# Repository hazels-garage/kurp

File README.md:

# Kurp
## 36 Key unibody split ortholinear

## PCB Render

Kurp is a choc-spaced unibody split ortholinear keyboard.

## Materials

| Description | Part | Count | Notes |
| :---: | :---: | :---: | :---: |
| PCBs | [Main](pcbs/pcb/jlcpcb/production_files) | 1 | |
|| [Switchplate](pcbs/switchplate/jlcpcb/production_files) | 1 | Optional |
|| [Backplate](pcbs/backplate/jlcpcb/production_files) | 1 | Optional |
|| [Centerplate](pcbs/centerplate/jlcpcb/production_files) | 1 | Optional |
| Controller | ProMicro footprint | 1 |  | 
| Diodes | 1N4148 SOD-123  | 36 |  |
| Switches | Choc v1 | 36 |  | 
| Keycaps | 1u | 36 | |
| Reset | TL3342F260QG | 1 | |
| Display | SSD1306 | 1 | Optional |
| | nice!view |  | Wireless Only |
| Power Switch |  MSK-12C02 | 1 | Wireless Only | 
| Battery Connector | TBD | 1 | Optional, Wireless Only | 
| Battery | TBD | 1 | Wireless Only |
| 3mm M2 Standoff ||8||
| 9mm M2 Standoff ||4||
| 3mm M2 Screw ||24||

## Firmware
QMK : https://github.com/hazels-garage/qmk_firmware/tree/hazel/kurp

ZMK: https://github.com/hazels-garage/zmk-kurp

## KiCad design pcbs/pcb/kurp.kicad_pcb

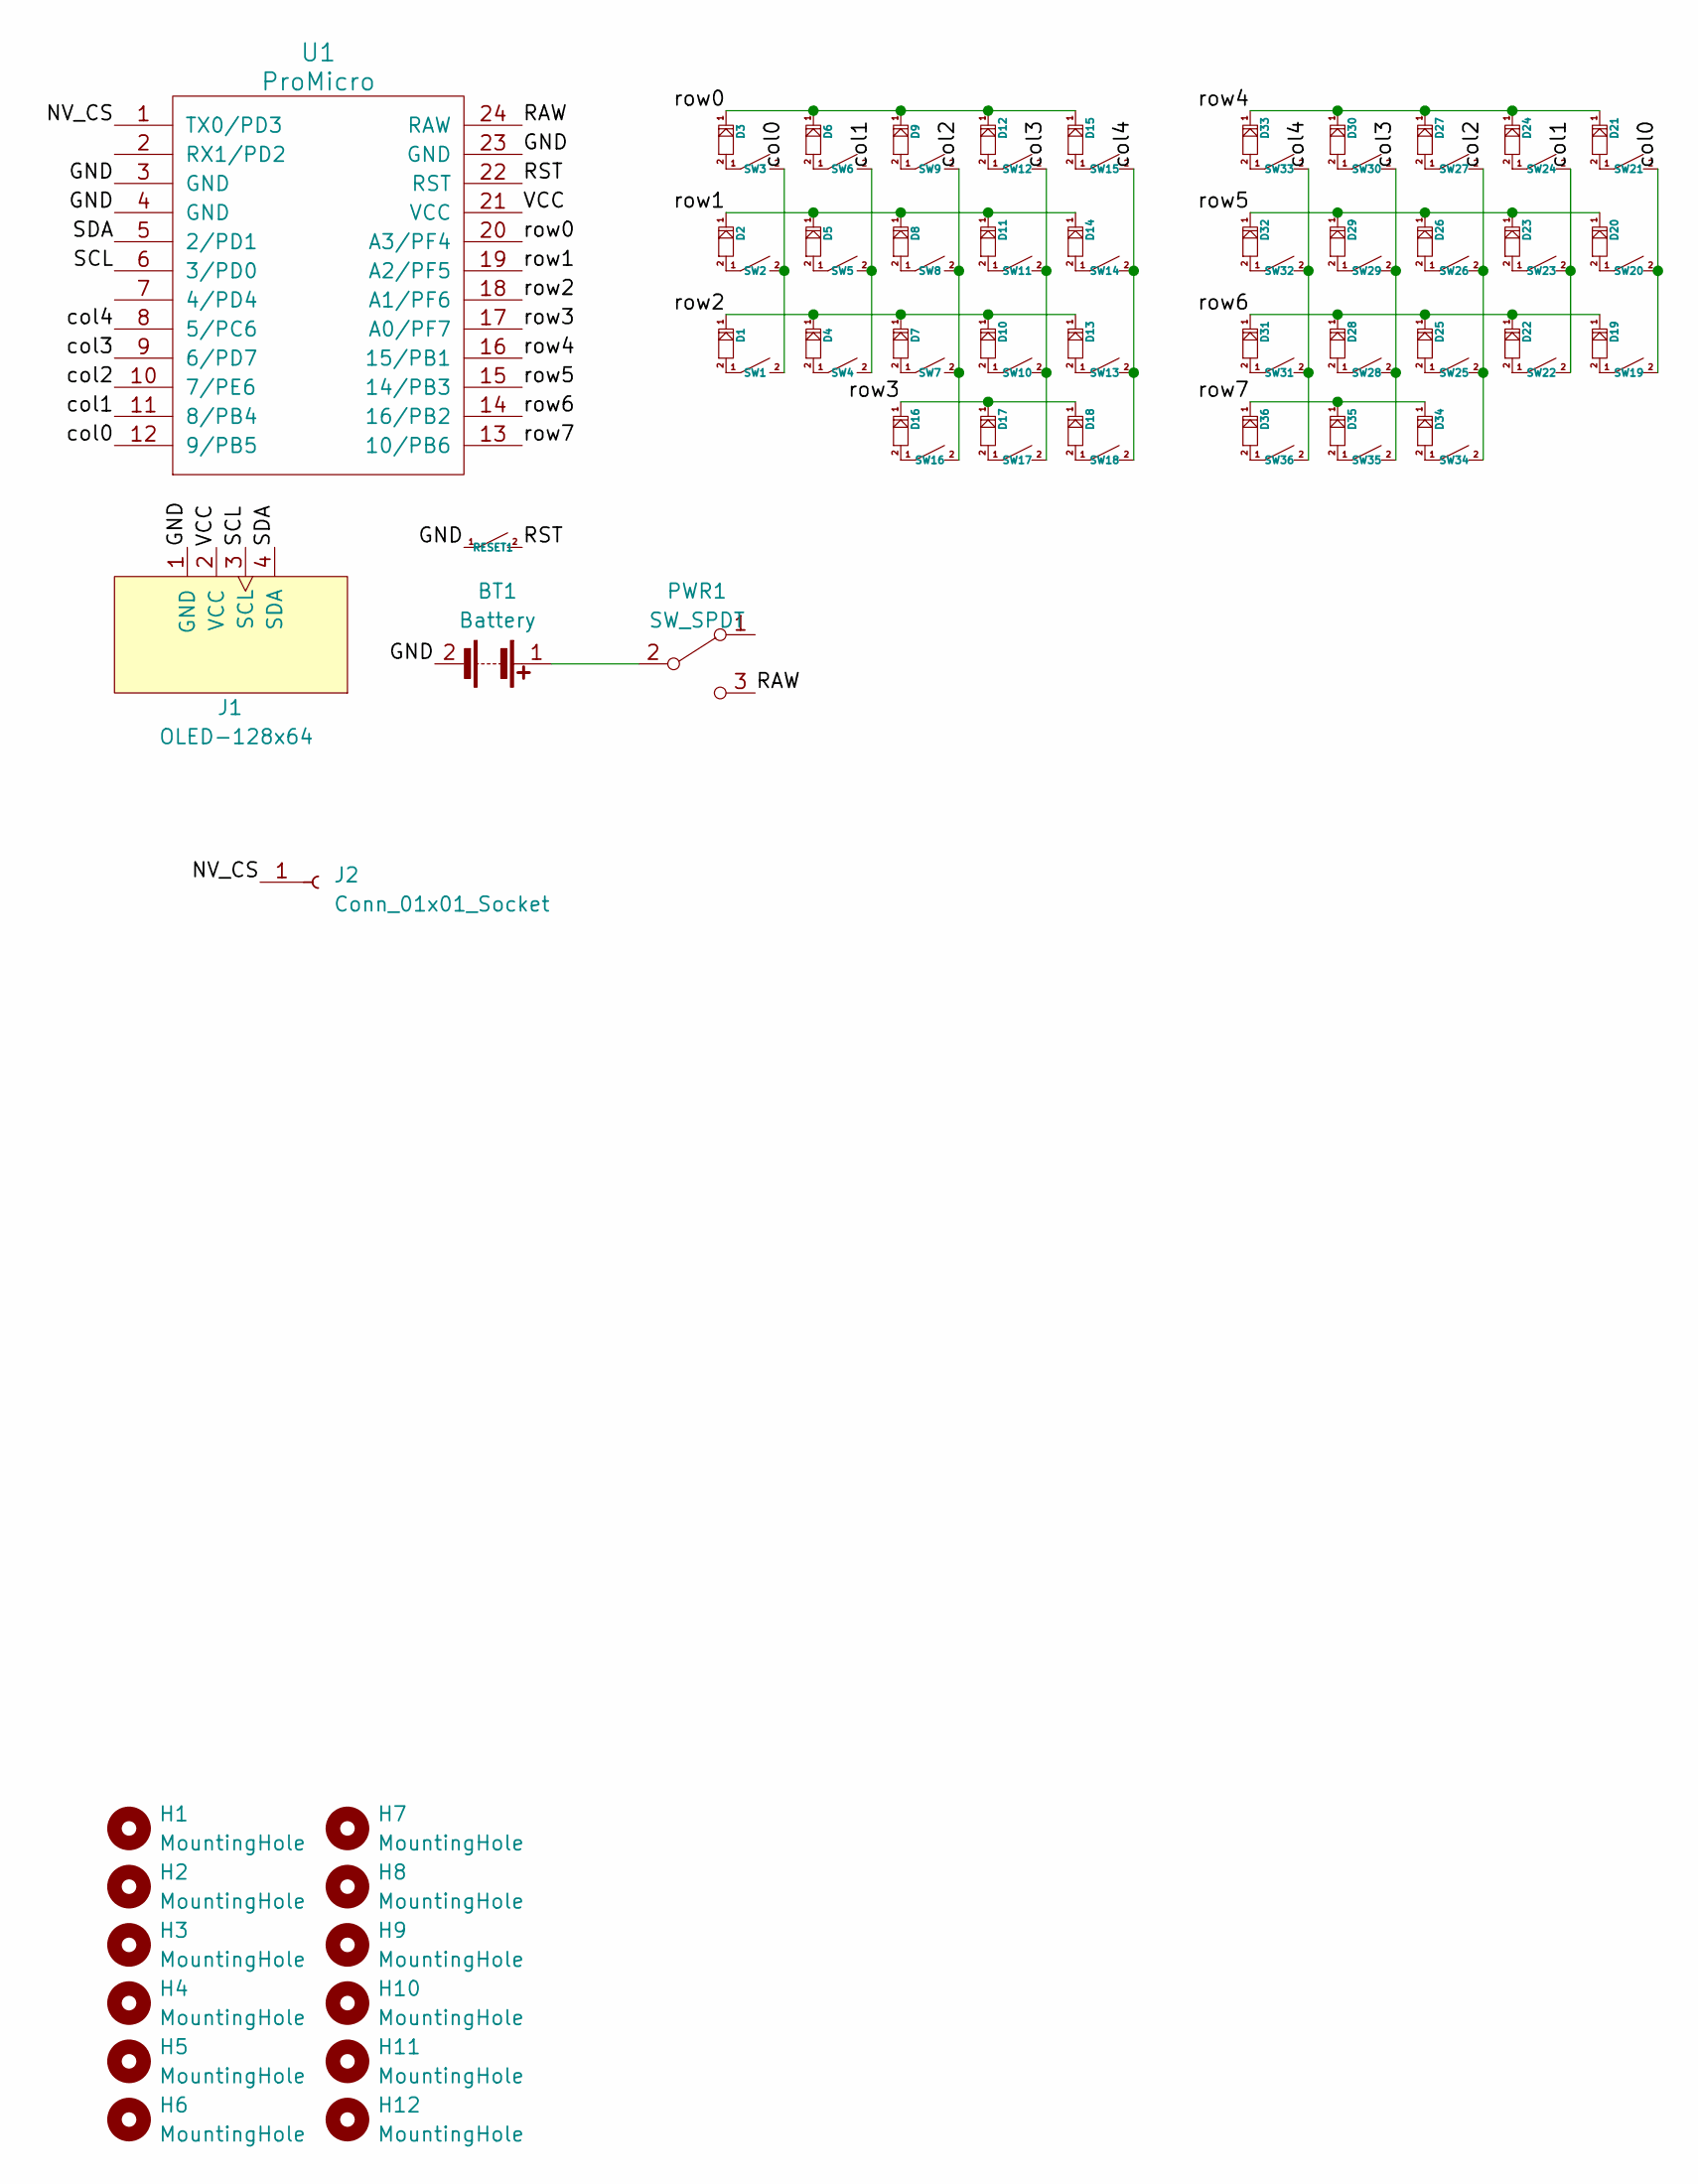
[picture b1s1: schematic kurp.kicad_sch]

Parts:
BT1: Battery; 3JST_BAT
D1, D2, D3, D4, D5, D6, D7, D8, D9, D10, D11, D12, D13, D14, D15, D16, D17, D18, D19, D20, D21, D22, D23, D24, D25, D26, D27, D28, D29, D30, D31, D32, D33, D34, D35, D36: D; D_SOD-123_via
H1, H2, H3, H4, H5, H6, H7, H8, H9, H10, H11, H12: MountingHole; MountingHole_3.2mm_M3_thinpad
J1: OLED-128x64
J2: Conn_01x01_Socket; CS_PIN
PWR1: SW_SPDT; SPDT_C128955
RESET1: SW; SW_SPST_TL3342
SW1, SW2, SW3, SW4, SW5, SW6, SW7, SW8, SW9, SW10, SW11, SW12, SW13, SW14, SW15, SW16, SW17, SW18, SW19, SW20, SW21, SW22, SW23, SW24, SW25, SW26, SW27, SW28, SW29, SW30, SW31, SW32, SW33, SW34, SW35, SW36: SW; jh-choc
U1: ProMicro; ArduinoProMicro

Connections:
/GND: BT1.2 (-), J1.1 (GND), RESET1.1, U1.3 (GND), U1.4 (GND), U1.23 (GND)
/NV_CS: J2.1, U1.1 (TX0/PD3)
/RAW: PWR1.3 (C), U1.24 (RAW)
/RST: RESET1.2, U1.22 (RST)
/SCL: J1.3 (SCL), U1.6 (3/PD0)
/SDA: J1.4 (SDA), U1.5 (2/PD1)
/VCC: J1.2 (VCC), U1.21 (VCC)
/col0: SW1.2, SW2.2, SW3.2, SW19.2, SW20.2, SW21.2, U1.12 (9/PB5)
/col1: SW4.2, SW5.2, SW6.2, SW22.2, SW23.2, SW24.2, U1.11 (8/PB4)
/col2: SW7.2, SW8.2, SW9.2, SW16.2, SW25.2, SW26.2, SW27.2, SW34.2, U1.10 (7/PE6)
/col3: SW10.2, SW11.2, SW12.2, SW17.2, SW28.2, SW29.2, SW30.2, SW35.2, U1.9 (6/PD7)
/col4: SW13.2, SW14.2, SW15.2, SW18.2, SW31.2, SW32.2, SW33.2, SW36.2, U1.8 (5/PC6)
/row0: D3.1, D6.1, D9.1, D12.1, D15.1, U1.20 (A3/PF4)
/row1: D2.1, D5.1, D8.1, D11.1, D14.1, U1.19 (A2/PF5)
/row2: D1.1, D4.1, D7.1, D10.1, D13.1, U1.18 (A1/PF6)
/row3: D16.1, D17.1, D18.1, U1.17 (A0/PF7)
/row4: D21.1, D24.1, D27.1, D30.1, D33.1, U1.16 (15/PB1)
/row5: D20.1, D23.1, D26.1, D29.1, D32.1, U1.15 (14/PB3)
/row6: D19.1, D22.1, D25.1, D28.1, D31.1, U1.14 (16/PB2)
/row7: D34.1, D35.1, D36.1, U1.13 (10/PB6)
unnamed: BT1.1 (+), PWR1.2 (B)
unnamed: D1.2, SW1.1
unnamed: D2.2, SW2.1
unnamed: D3.2, SW3.1
unnamed: D4.2, SW4.1
unnamed: D5.2, SW5.1
unnamed: D6.2, SW6.1
unnamed: D7.2, SW7.1
unnamed: D8.2, SW8.1
unnamed: D9.2, SW9.1
unnamed: D10.2, SW10.1
unnamed: D11.2, SW11.1
unnamed: D12.2, SW12.1
unnamed: D13.2, SW13.1
unnamed: D14.2, SW14.1
unnamed: D15.2, SW15.1
unnamed: D16.2, SW16.1
unnamed: D17.2, SW17.1
unnamed: D18.2, SW18.1
unnamed: D19.2, SW19.1
unnamed: D20.2, SW20.1
unnamed: D21.2, SW21.1
unnamed: D22.2, SW22.1
unnamed: D23.2, SW23.1
unnamed: D24.2, SW24.1
unnamed: D25.2, SW25.1
unnamed: D26.2, SW26.1
unnamed: D27.2, SW27.1
unnamed: D28.2, SW28.1
unnamed: D29.2, SW29.1
unnamed: D30.2, SW30.1
unnamed: D31.2, SW31.1
unnamed: D32.2, SW32.1
unnamed: D33.2, SW33.1
unnamed: D34.2, SW34.1
unnamed: D35.2, SW35.1
unnamed: D36.2, SW36.1

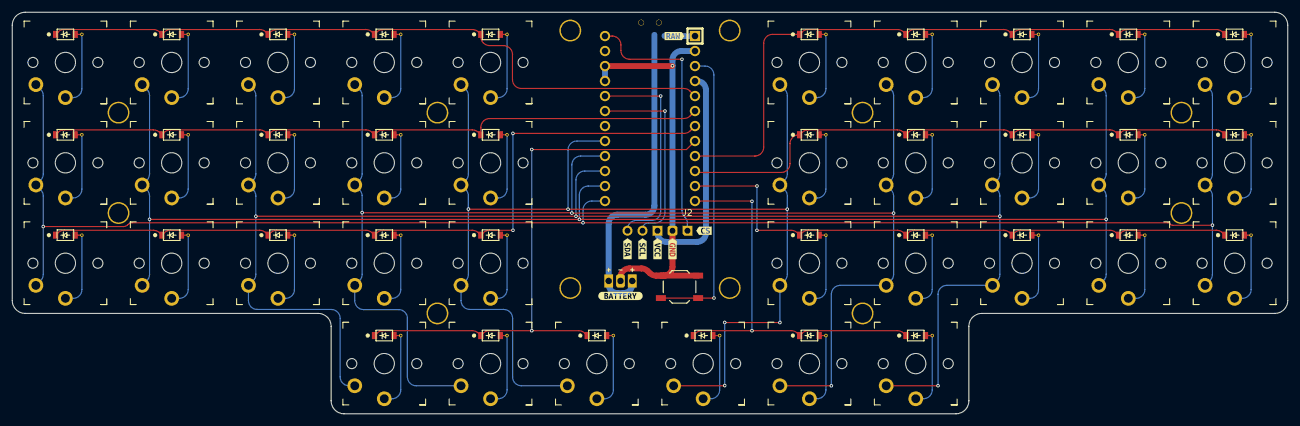
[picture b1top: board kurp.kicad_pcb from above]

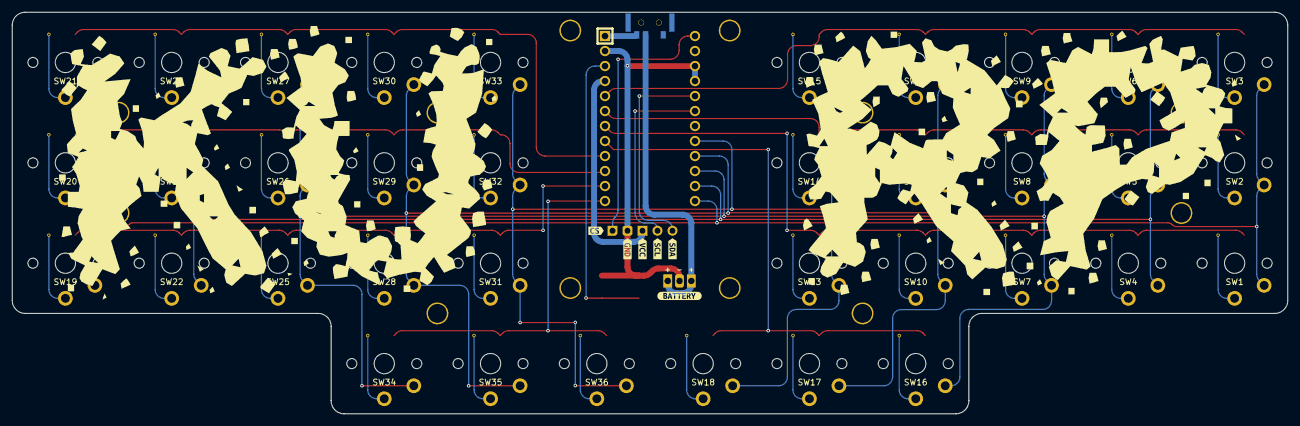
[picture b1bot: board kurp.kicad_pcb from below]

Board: 2 copper layers, 216.0 x 68.0 mm, 92 parts (3 on the bottom side), 57 nets.

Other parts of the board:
kibuzzard-641D257F: G***; kibuzzard-641D257F
kibuzzard-641D2588: G***; kibuzzard-641D2588

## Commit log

2023-03-24 init
2023-03-24 add license
2023-03-24 bump kicad version for kicad7
2023-03-24 Update gallery (automated)
2023-03-24 add links to pcb fab files
2023-04-07 added build image
2023-04-11 widen cutout for oled/niceview
2023-04-11 actually save pcb changes
2023-04-12 add qmk link
2023-09-02 add link to zmk-config
2024-01-27 adding case steps
2024-02-01 adding version of case with lower, uniform switch skirt
2026-03-26 Remove Hazel's Garage badge from README
    Removed badge for Hazel's Garage and associated link.

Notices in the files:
README.md:
https://img.shields.io/github/license/hazels-garage/kurp?label=%20&logo=creativecommons&logoColor=%23ffffff&style=flat-square
